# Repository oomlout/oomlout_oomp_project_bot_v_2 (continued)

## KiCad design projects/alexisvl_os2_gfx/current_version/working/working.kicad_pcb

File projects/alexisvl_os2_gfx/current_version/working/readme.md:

# os2
 
## summary 
* id: alexisvl_os2_gfx
* user: alexisvl
* name: os2
* board: gfx
* repo: https://github.com/alexisvl/os2
* src_file_repo_kicad_pcb: sch/gfx/gfx.kicad_pcb
* src_file_repo_kicad_pcb_link: https://github.com/alexisvl/os2/tree/trunk/sch/gfx/gfx.kicad_pcb
* src_file_repo_kicad_sch: sch/gfx/gfx.kicad_sch
* src_file_repo_kicad_sch_link: https://github.com/alexisvl/os2/tree/trunk/sch/gfx/gfx.kicad_sch

* src_file_repo_sch: sch/gfx/gfx.sch
* src_file_repo_sch_link: https://github.com/alexisvl/os2/tree/trunk/sch/gfx/gfx.sch
* full details link: https://github.com/oomlout/oomlout_oomp_project_bot_v_2/tree/main/projects/alexisvl_os2_gfx/current_version/working  

## schematic  
  
[schematic (pdf)](working_schematic.pdf) 

[schematic 1 (pdf)](working_1_schematic.pdf) 

## pcb  

[board (pdf)](working.pdf)  

## working_bom
| Id | Designator | Footprint | Quantity | Designation | Supplier and ref |  | None | 
| --- | --- | --- | --- | --- | --- | --- | --- | 
| 1 | R9,R33,R7,R8,R31 | R_Axial_DIN0207_L6.3mm_D2.5mm_P10.16mm_Horizontal | 5 | 499k |  |  | [''] | 
| 2 | R38,R23,R22,R37 | R_Axial_DIN0207_L6.3mm_D2.5mm_P10.16mm_Horizontal | 4 | 1k6 |  |  | [''] | 
| 3 | R18,R21 | R_Axial_DIN0207_L6.3mm_D2.5mm_P10.16mm_Horizontal | 2 | 4k99 |  |  | [''] | 
| 4 | C5,C1,C2,C3 | C_Disc_D4.7mm_W2.5mm_P5.00mm | 4 | 100p |  |  | [''] | 
| 5 | R34,R10,R36,R35,R32 | R_Axial_DIN0207_L6.3mm_D2.5mm_P10.16mm_Horizontal | 5 | 249k |  |  | [''] | 
| 6 | RV1,RV2 | stock_pot | 2 | 5k |  |  | [''] | 
| 7 | CD1 | CP_Radial_D8.0mm_P3.50mm | 1 | 470Âµ |  |  | [''] | 
| 8 | U18 | DIP-28_W15.24mm_Socket_LongPads | 1 | W27C512 |  |  | [''] | 
| 9 | P1 | DIN41612_B_3x32_Horizontal | 1 | DIN41612_M_3x32 |  |  | [''] | 
| 10 | CD40,CD43 | CP_Radial_D5.0mm_P2.00mm | 2 | 47Âµ |  |  | [''] | 
| 11 | D1,D3,D2 | D_DO-35_SOD27_P10.16mm_Horizontal | 3 | 1N4148 |  |  | [''] | 
| 12 | R2 | R_Axial_DIN0207_L6.3mm_D2.5mm_P10.16mm_Horizontal | 1 | 22k |  |  | [''] | 
| 13 | U8,U3,U7 | DIP-16_W7.62mm | 3 | 'HC109 |  |  | [''] | 
| 14 | Q4,Q6,Q1,Q7,Q5 | TO-92 | 5 | 2N3904 |  |  | [''] | 
| 15 | U11,U12,U13,U4 | DIP-16_W7.62mm | 4 | 'HC161 |  |  | [''] | 
| 16 | R30,R25 | R_Axial_DIN0207_L6.3mm_D2.5mm_P10.16mm_Horizontal | 2 | 6k2 |  |  | [''] | 
| 17 | R13,R12,R11,R14,R15 | R_Axial_DIN0207_L6.3mm_D2.5mm_P10.16mm_Horizontal | 5 | 68k |  |  | [''] | 
| 18 | RV6,RV3 | stock_pot | 2 | 50 |  |  | [''] | 
| 19 | Q3,Q2 | TO-92 | 2 | 2N7000 |  |  | [''] | 
| 20 | RV4 | stock_pot | 1 | 20k |  |  | [''] | 
| 21 | U10,U5,U9,U19 | DIP-14_W7.62mm | 4 | 'HC02 |  |  | [''] | 
| 22 | U15 | DIP-20_W7.62mm | 1 | 'AHC245 |  |  | [''] | 
| 23 | R41,R45,R26,R46 | R_Axial_DIN0207_L6.3mm_D2.5mm_P10.16mm_Horizontal | 4 | 75 |  |  | [''] | 
| 24 | U2 | DIP-14_W7.62mm | 1 | 'HC14 |  |  | [''] | 
| 25 | R3 | R_Axial_DIN0207_L6.3mm_D2.5mm_P10.16mm_Horizontal | 1 | 10k |  |  | [''] | 
| 26 | U21,U20 | DIP-8_W7.62mm | 2 | NE5532 |  |  | [''] | 
| 27 | RV5,RV7 | stock_pot | 2 | 10k |  |  | [''] | 
| 28 | R27,R42 | R_Axial_DIN0207_L6.3mm_D2.5mm_P10.16mm_Horizontal | 2 | 100 |  |  | [''] | 
| 29 | R40 | R_Axial_DIN0207_L6.3mm_D2.5mm_P10.16mm_Horizontal | 1 | 820 |  |  | [''] | 
| 30 | U14,U16 | DIP-20_W7.62mm | 2 | 'AHCT273 |  |  | [''] | 
| 31 | R20 | R_Axial_DIN0207_L6.3mm_D2.5mm_P10.16mm_Horizontal | 1 | 8k2 |  |  | [''] | 
| 32 | R4 | R_Axial_DIN0207_L6.3mm_D2.5mm_P10.16mm_Horizontal | 1 | 10 |  |  | [''] | 
| 33 | R24,R17 | R_Axial_DIN0207_L6.3mm_D2.5mm_P10.16mm_Horizontal | 2 | 7k5 |  |  | [''] | 
| 34 | R6 | R_Axial_DIN0207_L6.3mm_D2.5mm_P10.16mm_Horizontal | 1 | 3k3 |  |  | [''] | 
| 35 | R39 | R_Axial_DIN0207_L6.3mm_D2.5mm_P10.16mm_Horizontal | 1 | 3k |  |  | [''] | 
| 36 | R28,R43,R29,R44 | R_Axial_DIN0309_L9.0mm_D3.2mm_P12.70mm_Horizontal | 4 | 1k |  |  | [''] | 
| 37 | U1 | Oscillator_DIP-8 | 1 | 1MHz |  |  | [''] | 
| 38 | R1 | R_Axial_DIN0207_L6.3mm_D2.5mm_P10.16mm_Horizontal | 1 | 82k |  |  | [''] | 
| 39 | U17 | DIP-16_W7.62mm | 1 | 'HC237 |  |  | [''] | 
| 40 | U6 | DIP-14_W7.62mm | 1 | 'HC10 |  |  | [''] | 
| 41 | RN1 | R_Array_SIP10 | 1 | 1k |  |  | [''] | 
| 42 | R16 | R_Axial_DIN0207_L6.3mm_D2.5mm_P10.16mm_Horizontal | 1 | 15k |  |  | [''] | 
| 43 | R5 | R_Axial_DIN0207_L6.3mm_D2.5mm_P10.16mm_Horizontal | 1 | 6k8 |  |  | [''] | 
| 44 | R19 | R_Axial_DIN0207_L6.3mm_D2.5mm_P10.16mm_Horizontal | 1 | 18k |  |  | [''] | 
| 45 | CD18,CD45,CD17,CD15,CD11,CD21,CD2,CD12,CD4,CD41,CD20,CD3,CD10,CD14,CD7,CD8,CD13,CD6,CD9,CD44,CD16,CD5,CD19,CD42 | C_0805_2012Metric_Pad1.15x1.40mm_HandSolder | 24 | 1Âµ |  |  | [''] | 

## bom_schematic
no data

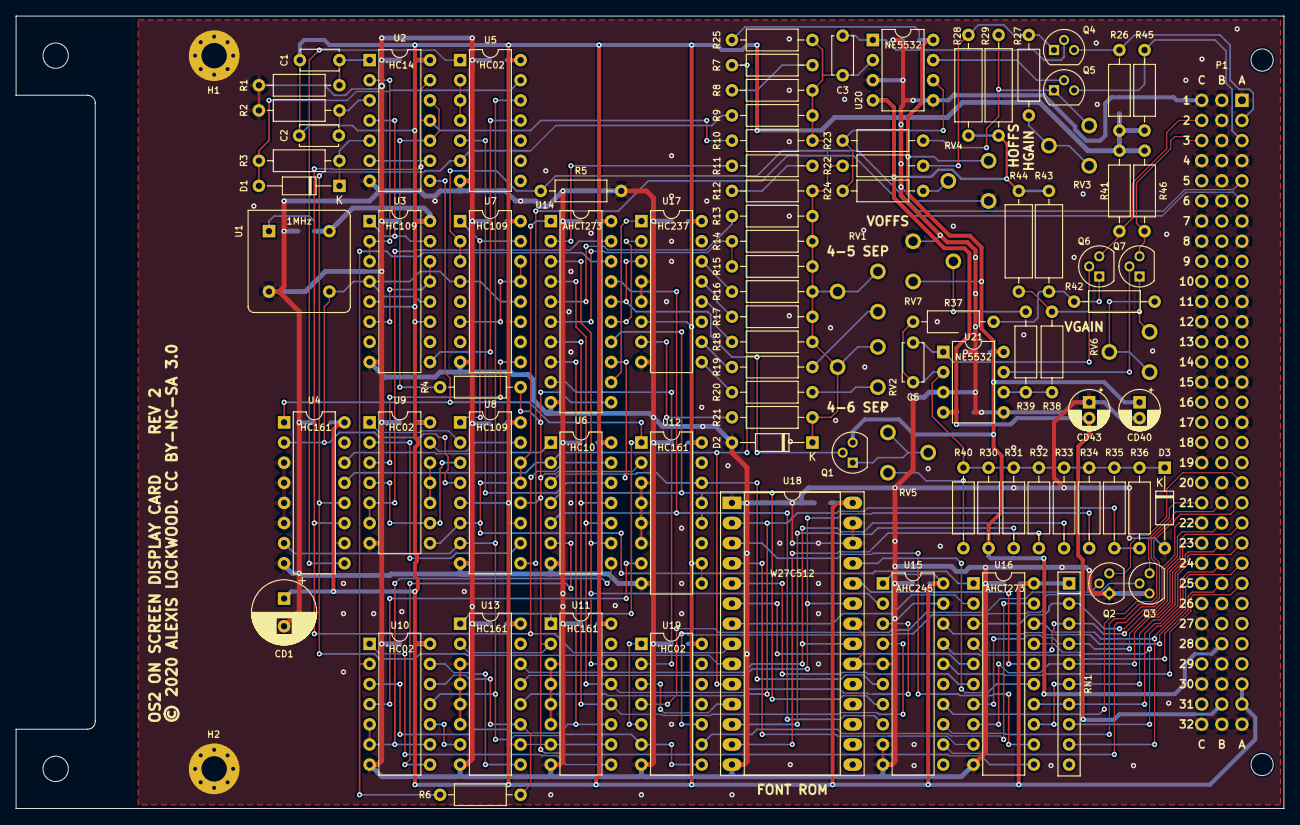
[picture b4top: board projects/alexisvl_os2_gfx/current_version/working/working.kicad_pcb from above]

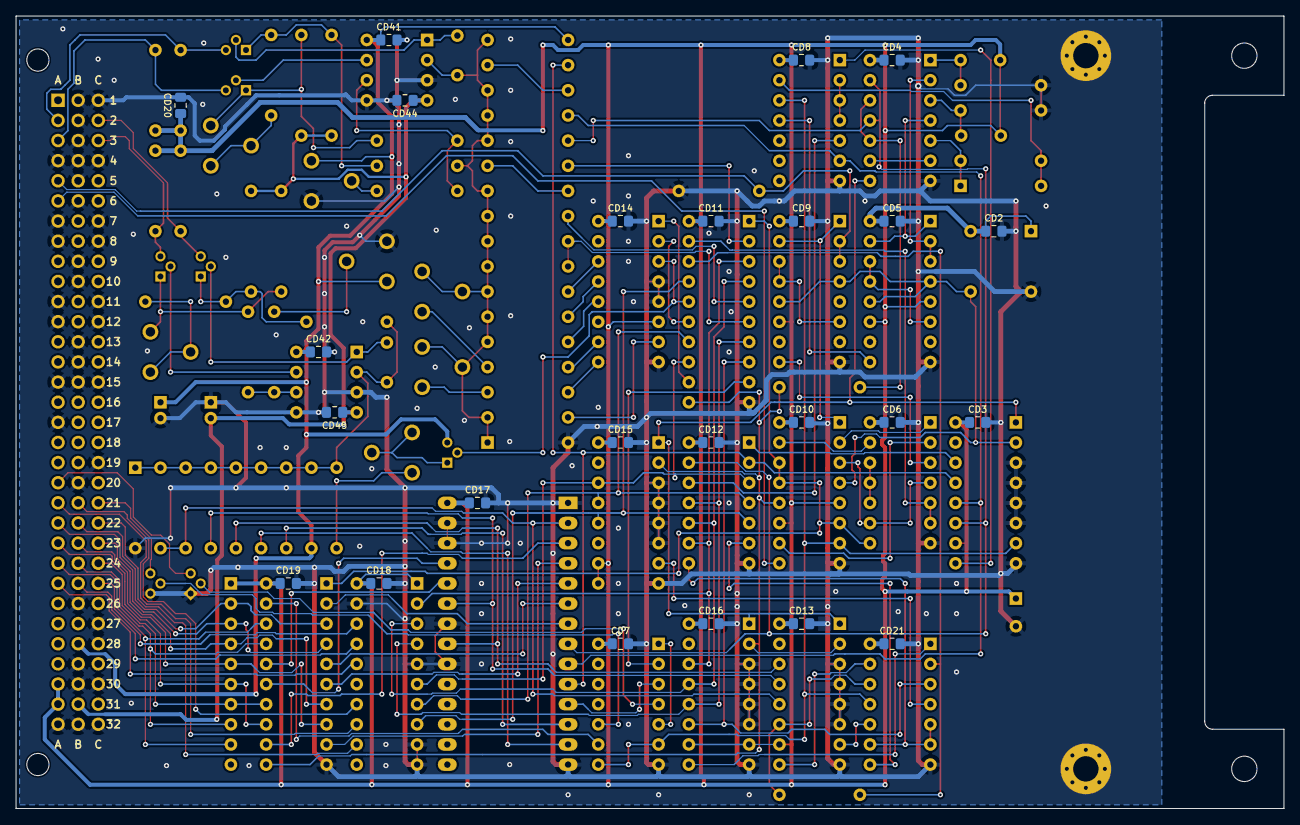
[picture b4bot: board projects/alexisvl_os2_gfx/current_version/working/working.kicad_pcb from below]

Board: 2 copper layers, 160.0 x 100.0 mm, 119 parts (24 on the bottom side), 124 nets.

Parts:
C1, C2, C3, C5: 100p; C_Disc_D4.7mm_W2.5mm_P5.00mm
CD1: 470µ; CP_Radial_D8.0mm_P3.50mm
CD2, CD3, CD4, CD5, CD6, CD7, CD8, CD9, CD10, CD11, CD12, CD13, CD14, CD15, CD16, CD17, CD18, CD19, CD20, CD21, CD41, CD42, CD44, CD45: 1µ; C_0805_2012Metric_Pad1.15x1.40mm_HandSolder
CD40, CD43: 47µ; CP_Radial_D5.0mm_P2.00mm
D1, D2, D3: 1N4148; D_DO-35_SOD27_P10.16mm_Horizontal
H1, H2: HOLE; MountingHole_3.2mm_M3_Pad_Via
P1: DIN41612_M_3x32; DIN41612_B_3x32_Horizontal
Q1, Q4, Q5, Q6, Q7: 2N3904; TO-92
Q2, Q3: 2N7000; TO-92
R1: 82k; R_Axial_DIN0207_L6.3mm_D2.5mm_P10.16mm_Horizontal
R2: 22k; R_Axial_DIN0207_L6.3mm_D2.5mm_P10.16mm_Horizontal
R3: 10k; R_Axial_DIN0207_L6.3mm_D2.5mm_P10.16mm_Horizontal
R4: 10; R_Axial_DIN0207_L6.3mm_D2.5mm_P10.16mm_Horizontal
R5: 6k8; R_Axial_DIN0207_L6.3mm_D2.5mm_P10.16mm_Horizontal
R6: 3k3; R_Axial_DIN0207_L6.3mm_D2.5mm_P10.16mm_Horizontal
R7, R8, R9, R31, R33: 499k; R_Axial_DIN0207_L6.3mm_D2.5mm_P10.16mm_Horizontal
R10, R32, R34, R35, R36: 249k; R_Axial_DIN0207_L6.3mm_D2.5mm_P10.16mm_Horizontal
R11, R12, R13, R14, R15: 68k; R_Axial_DIN0207_L6.3mm_D2.5mm_P10.16mm_Horizontal
R16: 15k; R_Axial_DIN0207_L6.3mm_D2.5mm_P10.16mm_Horizontal
R17, R24: 7k5; R_Axial_DIN0207_L6.3mm_D2.5mm_P10.16mm_Horizontal
R18, R21: 4k99; R_Axial_DIN0207_L6.3mm_D2.5mm_P10.16mm_Horizontal
R19: 18k; R_Axial_DIN0207_L6.3mm_D2.5mm_P10.16mm_Horizontal
R20: 8k2; R_Axial_DIN0207_L6.3mm_D2.5mm_P10.16mm_Horizontal
R22, R23, R37, R38: 1k6; R_Axial_DIN0207_L6.3mm_D2.5mm_P10.16mm_Horizontal
R25, R30: 6k2; R_Axial_DIN0207_L6.3mm_D2.5mm_P10.16mm_Horizontal
R26, R41, R45, R46: 75; R_Axial_DIN0207_L6.3mm_D2.5mm_P10.16mm_Horizontal
R27, R42: 100; R_Axial_DIN0207_L6.3mm_D2.5mm_P10.16mm_Horizontal
R28, R29, R43, R44: 1k; R_Axial_DIN0309_L9.0mm_D3.2mm_P12.70mm_Horizontal
R39: 3k; R_Axial_DIN0207_L6.3mm_D2.5mm_P10.16mm_Horizontal
R40: 820; R_Axial_DIN0207_L6.3mm_D2.5mm_P10.16mm_Horizontal
RN1: 1k; R_Array_SIP10
RV1, RV2: 5k; stock_pot
RV3, RV6: 50; stock_pot
RV4: 20k; stock_pot
RV5, RV7: 10k; stock_pot
U1: 1MHz; Oscillator_DIP-8
U2: 'HC14; DIP-14_W7.62mm
U3, U7, U8: 'HC109; DIP-16_W7.62mm
U4, U11, U12, U13: 'HC161; DIP-16_W7.62mm
U5, U9, U10, U19: 'HC02; DIP-14_W7.62mm
U6: 'HC10; DIP-14_W7.62mm
U14, U16: 'AHCT273; DIP-20_W7.62mm
U15: 'AHC245; DIP-20_W7.62mm
U17: 'HC237; DIP-16_W7.62mm
U18: W27C512; DIP-28_W15.24mm_Socket_LongPads
U20, U21: NE5532; DIP-8_W7.62mm

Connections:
+15V: CD40.1, CD41.1, CD42.1, P1.B28, Q1.3 (C), R25.2, R30.2, RV4.3, RV7.3, U20.8 (V+), U21.8 (V+)
-15V: CD43.2, CD44.1, CD45.1, P1.B31, R28.1, R29.1, R43.1, R44.1, U20.4 (V-), U21.4 (V-)
/CHAR0: U16.2 (Q0), U18.7 (A3)
/CHAR1: U16.5 (Q1), U18.6 (A4)
/CHAR2: U16.6 (Q2), U18.5 (A5)
/CHAR3: U16.9 (Q3), U18.4 (A6)
/CHAR4: U16.12 (Q4), U18.3 (A7)
/CHAR5: U16.15 (Q5), U18.25 (A8)
/CHAR6: U16.16 (Q6), U18.24 (A9)
/DESCENDER0: R31.2, U18.12 (D1)
/DESCENDER1: R32.2, U18.13 (D2)
/DONE#: U8.10 (Q), U9.2
/DONEREQ: U9.5, U9.6, U14.19 (Q7)
/FLD0: U14.12 (Q4), U17.1 (A0)
/FLD1: U14.15 (Q5), U17.2 (A1)
/FLD2: Q1.2 (B), U14.16 (Q6), U17.3 (A2)
/FLDREQ0: U6.3, U12.14 (Q0), U14.13 (D4), U15.6 (A4)
/FLDREQ1: U6.4, U12.13 (Q1), U14.14 (D5), U15.7 (A5)
/FLDREQ2: U6.5, U12.12 (Q2), U14.17 (D6), U15.8 (A6)
/HDOT0: R7.2, U4.13 (Q1), U6.2, U18.10 (A0)
/HDOT1: R9.2, U4.12 (Q2), U5.6, U18.9 (A1)
/HDOT2: R10.2, U2.11, U2.13, U4.11 (Q3), U6.13, U18.8 (A2)
/INTEN#: U16.19 (Q7), U19.9
/INTERFIELD_BLANK: U14.9 (Q3), U19.2
/LASTDOT: U4.9 (~Pe), U5.1
/LASTFLD#: U6.6, U10.8
/LASTPOS#: U6.8, U10.5, U10.6, U10.9
/LINE0: R33.2, U13.14 (Q0), U18.21 (A10)
/LINE1: R34.2, U13.13 (Q1), U18.23 (A11)
/LINE2: R35.2, R36.2, U13.12 (Q2), U18.2 (A12)
/PIX_BLANK: U18.11 (D0), U19.3
/POS0: R11.2, U14.2 (Q0)
/POS1: R13.2, U14.5 (Q1)
/POS2: R14.2, R15.2, U14.6 (Q2)
/POSREQ0: U6.9, U11.14 (Q0), U14.3 (D0), U15.2 (A0)
/POSREQ1: U6.10, U11.13 (Q1), U14.4 (D1), U15.3 (A1)
/POSREQ2: U6.11, U11.12 (Q2), U14.7 (D2), U15.4 (A2)
/PREBLANK: U10.3, U11.11 (Q3), U14.8 (D3)
/PREDONE: R6.2, U10.12, U13.11 (Q3)
/PREDONE': R6.1, U10.2, U14.18 (D7)
/~POR: U7.1 (R), U7.15 (R), U8.1 (R)
A2: P1.A2, Q4.3 (C), R26.1
A3: P1.A3, Q5.3 (C), R45.2
A5: P1.A5, R5.2, U7.2 (J), U7.3 (K)
A6: P1.A6, U8.9 (Q)
A20: P1.A20, Q2.3 (D)
A21: P1.A21, U15.13 (B5)
A22: P1.A22, RN1.3 (R2), U16.4 (D1)
A23: P1.A23, RN1.6 (R5), U16.13 (D4)
A24: P1.A24, RN1.9 (R8), U16.18 (D7)
A25: P1.A25, U15.16 (B2)
B21: P1.B21, U15.14 (B4)
B22: P1.B22, RN1.2 (R1), U16.3 (D0)
B23: P1.B23, RN1.5 (R4), U16.8 (D3)
B24: P1.B24, RN1.8 (R7), U16.17 (D6)
B25: P1.B25, U15.17 (B1)
C2: P1.C2, Q6.3 (C), R41.1
C3: P1.C3, Q7.3 (C), R46.2
C21: P1.C21, Q3.3 (D)
C22: P1.C22, U15.12 (B6)
C23: P1.C23, RN1.4 (R3), U16.7 (D2)
C24: P1.C24, RN1.7 (R6), U16.14 (D5)
C25: P1.C25, U15.18 (B0)
CLK: U1.5 (OUT), U3.4 (C), U3.12 (C), U4.2 (CK), U7.4 (C), U7.12 (C), U8.4 (C)
GND: CD1.2, CD2.2, CD3.2, CD4.2, CD5.2, CD6.2, CD7.2, CD8.2, CD9.2, CD10.2, CD11.2, CD12.2, CD13.2, CD14.2, CD15.2, CD16.2, CD17.2, CD18.2, CD19.2, CD20.2, CD21.2, CD40.2, CD41.2, CD42.2, CD43.1, CD44.2, CD45.2, D2.2 (A), D3.2 (A), H1.1, H2.1, P1.A1, P1.A4, P1.A7, P1.A8, P1.A11, P1.A12, P1.A15, P1.A17, P1.A32, P1.B1, P1.B2, P1.B3, P1.B4, P1.B5, P1.B6, P1.B9, P1.B10, P1.B13, P1.B14, P1.B15, P1.B20, P1.B26, P1.B29, P1.B30, P1.B32, P1.C1, P1.C4, P1.C7, P1.C8, P1.C11, P1.C12, P1.C15, P1.C19, P1.C27, P1.C28, P1.C30, P1.C32, Q2.1 (S), Q3.1 (S), R1.2, R2.2, R5.1, RV4.1, RV7.1, U1.4 (GND), U2.7 (GND), U3.8 (GND), U4.3 (P0), U4.4 (P1), U4.5 (P2), U4.6 (P3), U4.8 (GND), U5.7 (GND), U6.7 (GND), U7.8 (GND), U8.8 (GND), U9.7 (GND), U10.7 (GND), U11.3 (P0), U11.4 (P1), U11.5 (P2), U11.6 (P3), U11.8 (GND), U12.3 (P0), U12.4 (P1), U12.5 (P2), U12.6 (P3), U12.8 (GND), U13.3 (P0), U13.4 (P1), U13.5 (P2), U13.6 (P3), U13.8 (GND), U14.10 (GND), U15.5 (A3), U15.9 (A7), U15.10 (GND), U15.19 (CE), U16.10 (GND), U17.4 (~LE), U17.5 (~E1), U17.8 (GND), U18.1 (A15), U18.14 (GND), U18.20 (~CE), U18.22 (~OE), U18.26 (A13), U18.27 (A14), U19.7 (GND), U20.3 (+), U20.5 (+), U21.3 (+), U21.5 (+)
unnamed: C1.2, R1.1, U2.1
unnamed: C2.2, R2.1, U2.3
unnamed: C3.1, D2.1 (K), R8.1, R9.1, R10.1, R12.1, R13.1, R14.1, R15.1, R16.1, R17.1, R18.1, R21.1, R22.1, R25.1, RV1.2, RV1.3, RV2.2, RV2.3, U20.2 (-)
unnamed: C3.2, Q4.2 (B), U20.1
unnamed: C5.1, D3.1 (K), R30.1, R31.1, R32.1, R33.1, R34.1, R35.1, R36.1, R37.1, R40.1, U21.2 (-)
unnamed: C5.2, Q6.2 (B), U21.1
unnamed: D1.1 (K), R3.2, U2.5
unnamed: D1.2 (A), R3.1, U5.13
unnamed: Q1.1 (E), RV5.1, RV5.2
unnamed: Q2.2 (G), U19.4
unnamed: Q3.2 (G), U19.10
unnamed: Q4.1 (E), R22.2, R27.1, R28.2
unnamed: Q5.1 (E), R23.1, R29.2, RV3.3
unnamed: Q5.2 (B), U20.7
unnamed: Q6.1 (E), R37.2, R42.1, R43.2
unnamed: Q7.1 (E), R38.1, R44.2, RV6.3
unnamed: Q7.2 (B), U21.7
unnamed: R4.1, U2.10, U2.12
unnamed: R7.1, R8.2
unnamed: R11.1, R12.2
unnamed: R16.2, U17.14 (Y1)
unnamed: R17.2, U17.13 (Y2)
unnamed: R18.2, U17.12 (Y3)
unnamed: R19.1, RV1.1
unnamed: R19.2, U17.10 (Y5)
unnamed: R20.1, RV2.1
unnamed: R20.2, U17.9 (Y6)
unnamed: R21.2, U17.7 (Y7)
unnamed: R23.2, R24.1, U20.6 (-)
unnamed: R24.2, RV4.2
unnamed: R27.2, RV3.1, RV3.2
unnamed: R38.2, R39.1, U21.6 (-)
unnamed: R39.2, RV7.2
unnamed: R40.2, RV5.3
unnamed: R42.2, RV6.1, RV6.2
unnamed: U2.2, U3.2 (J), U3.3 (K)
unnamed: U2.4, U3.1 (R), U3.15 (R)
unnamed: U2.6, U2.9
unnamed: U3.6 (Q), U3.13 (K), U3.14 (J)
unnamed: U4.14 (Q0), U6.1
unnamed: U5.2, U5.3, U5.4
unnamed: U5.5, U6.12
unnamed: U7.9 (Q), U9.3
unnamed: U7.6 (Q), U7.13 (K), U7.14 (J)
unnamed: U8.2 (J), U9.1
unnamed: U8.3 (K), U9.4, U9.9
unnamed: U8.15 (R), U9.13
unnamed: U9.10, U9.11, U9.12
unnamed: U10.1, U11.9 (~Pe)
unnamed: U10.4, U12.7 (ENP)
unnamed: U10.10, U13.7 (ENP)
unnamed: U10.13, U13.9 (~Pe)
unnamed: U19.1, U19.5
POR: U3.9 (Q), U5.11
POSCLK: R4.2, U8.12 (C), U11.2 (CK), U12.2 (CK), U13.2 (CK), U14.11 (Cp), U16.11 (Cp)
RST#: U2.8, U4.1 (~MR), U11.1 (~MR), U12.1 (~MR), U13.1 (~MR)
RUN: U8.6 (Q), U8.13 (K), U8.14 (J), U9.8, U14.1 (~Mr), U16.1 (~Mr)
RUN#: U4.7 (ENP), U5.12, U8.7 (Q), U10.11, U19.6, U19.8
VCC: C1.1, C2.1, CD1.1, CD2.1, CD3.1, CD4.1, CD5.1, CD6.1, CD7.1, CD8.1, CD9.1, CD10.1, CD11.1, CD12.1, CD13.1, CD14.1, CD15.1, CD16.1, CD17.1, CD18.1, CD19.1, CD20.1, CD21.1, P1.A30, P1.A31, R26.2, R41.2, R45.1, R46.1, RN1.1 (common), U1.1 (EN), U1.8 (Vcc), U2.14 (VCC), U3.5 (S), U3.11 (S), U3.16 (VCC), U4.10 (ENT), U4.16 (VCC), U5.14 (VCC), U6.14 (VCC), U7.11 (S), U7.16 (VCC), U8.5 (S), U8.11 (S), U8.16 (VCC), U9.14 (VCC), U10.14 (VCC), U11.7 (ENP), U11.10 (ENT), U11.16 (VCC), U12.9 (~Pe), U12.10 (ENT), U12.16 (VCC), U13.10 (ENT), U13.16 (VCC), U14.20 (VCC), U15.1 (A->B), U15.20 (VCC), U16.20 (VCC), U17.6 (E2), U17.16 (VCC), U18.28 (VCC), U19.14 (VCC)

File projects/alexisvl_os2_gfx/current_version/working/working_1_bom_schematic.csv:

"Source:","C:\gh\oomlout_oomp_project_bot_v_2\projects\alexisvl_os2_gfx\current_version\working\working_1.kicad_sch"
"Date:","24/09/2023 22:51:26"
"Tool:","Eeschema 7.0.6"
"Generator:","C:/Program Files/KiCad/7.0/bin/scripting/plugins/bom_csv_grouped_by_value_with_fp.py"
"Component Count:","119"
"Ref","Qnty","Value","Cmp name","Footprint","Description","Vendor","DNP"
"C1, C2, C3, C5","4","100p","C","Capacitor_THT:C_Disc_D4.7mm_W2.5mm_P5.00mm","","",""
"CD1","1","470µ","CP","Capacitor_THT:CP_Radial_D8.0mm_P3.50mm","","",""
"CD2, CD3, CD4, CD5, CD6, CD7, CD8, CD9, CD10, CD11, CD12, CD13, CD14, CD15, CD16, CD17, CD18, CD19, CD20, CD21, CD41, CD42, CD44, CD45","24","1µ","C","Capacitor_SMD:C_0805_2012Metric_Pad1.15x1.40mm_HandSolder","","",""
"CD40, CD43","2","47µ","CP","Capacitor_THT:CP_Radial_D5.0mm_P2.00mm","","",""
"D1, D2, D3","3","1N4148","D","Diode_THT:D_DO-35_SOD27_P10.16mm_Horizontal","","",""
"H1, H2","2","HOLE","Conn_01x01_Male","MountingHole:MountingHole_3.2mm_M3_Pad_Via","Generic connector, single row, 01x01, script generated (kicad-library-utils/schlib/autogen/connector/)","",""
"P1","1","DIN41612_M_3x32","DIN41612_M_3x32","alt-libs:DIN41612_B_3x32_Horizontal","","",""
"Q1, Q4, Q5, Q6, Q7","5","2N3904","Q_NPN_EBC","Package_TO_SOT_THT:TO-92","","",""
"Q2, Q3","2","2N7000","Q_NMOS_SGD","Package_TO_SOT_THT:TO-92","","",""
"R1","1","82k","R","Resistor_THT:R_Axial_DIN0207_L6.3mm_D2.5mm_P10.16mm_Horizontal","","",""
"R2","1","22k","R","Resistor_THT:R_Axial_DIN0207_L6.3mm_D2.5mm_P10.16mm_Horizontal","","",""
"R3","1","10k","R","Resistor_THT:R_Axial_DIN0207_L6.3mm_D2.5mm_P10.16mm_Horizontal","","",""
"R4","1","10","R","Resistor_THT:R_Axial_DIN0207_L6.3mm_D2.5mm_P10.16mm_Horizontal","","",""
"R5","1","6k8","R","Resistor_THT:R_Axial_DIN0207_L6.3mm_D2.5mm_P10.16mm_Horizontal","","",""
"R6","1","3k3","R","Resistor_THT:R_Axial_DIN0207_L6.3mm_D2.5mm_P10.16mm_Horizontal","","",""
"R7, R8, R9, R31, R33","5","499k","R","Resistor_THT:R_Axial_DIN0207_L6.3mm_D2.5mm_P10.16mm_Horizontal","","",""
"R10, R32, R34, R35, R36","5","249k","R","Resistor_THT:R_Axial_DIN0207_L6.3mm_D2.5mm_P10.16mm_Horizontal","","",""
"R11, R12, R13, R14, R15","5","68k","R","Resistor_THT:R_Axial_DIN0207_L6.3mm_D2.5mm_P10.16mm_Horizontal","","",""
"R16","1","15k","R","Resistor_THT:R_Axial_DIN0207_L6.3mm_D2.5mm_P10.16mm_Horizontal","","",""
"R17, R24","2","7k5","R","Resistor_THT:R_Axial_DIN0207_L6.3mm_D2.5mm_P10.16mm_Horizontal","","",""
"R18, R21","2","4k99","R","Resistor_THT:R_Axial_DIN0207_L6.3mm_D2.5mm_P10.16mm_Horizontal","","",""
"R19","1","18k","R","Resistor_THT:R_Axial_DIN0207_L6.3mm_D2.5mm_P10.16mm_Horizontal","","",""
"R20","1","8k2","R","Resistor_THT:R_Axial_DIN0207_L6.3mm_D2.5mm_P10.16mm_Horizontal","","",""
"R22, R23, R37, R38","4","1k6","R","Resistor_THT:R_Axial_DIN0207_L6.3mm_D2.5mm_P10.16mm_Horizontal","","",""
"R25, R30","2","6k2","R","Resistor_THT:R_Axial_DIN0207_L6.3mm_D2.5mm_P10.16mm_Horizontal","","",""
"R26, R41, R45, R46","4","75","R","Resistor_THT:R_Axial_DIN0207_L6.3mm_D2.5mm_P10.16mm_Horizontal","","",""
"R27, R42","2","100","R","Resistor_THT:R_Axial_DIN0207_L6.3mm_D2.5mm_P10.16mm_Horizontal","","",""
"R28, R29, R43, R44","4","1k","R_HW","Resistor_THT:R_Axial_DIN0309_L9.0mm_D3.2mm_P12.70mm_Horizontal","","",""
"R39","1","3k","R","Resistor_THT:R_Axial_DIN0207_L6.3mm_D2.5mm_P10.16mm_Horizontal","","",""
"R40","1","820","R","Resistor_THT:R_Axial_DIN0207_L6.3mm_D2.5mm_P10.16mm_Horizontal","","",""
"RN1","1","1k","R_Network09","Resistor_THT:R_Array_SIP10","9 resistor network, star topology, bussed resistors, small symbol","",""
"RV1, RV2","2","5k","AltDevice:R_POT_TRIM_7","alt-libs:stock_pot","","",""
"RV3, RV6","2","50","AltDevice:R_POT_TRIM_2","alt-libs:stock_pot","","",""
"RV4","1","20k","AltDevice:R_POT_TRIM_4","alt-libs:stock_pot","","",""
"RV5, RV7","2","10k","AltDevice:R_POT_TRIM_3","alt-libs:stock_pot","","",""
"U1","1","1MHz","CXO_DIP8","Oscillator:Oscillator_DIP-8","Crystal Clock Oscillator, DIP8-style metal package","",""
"U2","1","'HC14","74HC14","Package_DIP:DIP-14_W7.62mm","","",""
"U3, U7, U8","3","'HC109","AltDevice:74LS109_6","Package_DIP:DIP-16_W7.62mm","","",""
"U4, U11, U12, U13","4","'HC161","74LS161","Package_DIP:DIP-16_W7.62mm","","",""
"U5, U9, U10, U19","4","'HC02","74HC02","Package_DIP:DIP-14_W7.62mm","quad 2-input NOR gate","",""
"U6","1","'HC10","74LS10","Package_DIP:DIP-14_W7.62mm","Triple 3-input NAND","",""
"U14, U16","2","'AHCT273","74HC273","Package_DIP:DIP-20_W7.62mm","8-bit D Flip-Flop, reset","",""
"U15","1","'AHC245","74LS245","Package_DIP:DIP-20_W7.62mm","Octal BUS Transceivers, 3-State outputs","",""
"U17","1","'HC237","74HC237","Package_DIP:DIP-16_W7.62mm","3-to-8 line decoder/multiplexer with address latches, DIP-16/SOIC-16/SSOP-16","",""
"U18","1","W27C512","27C512","Package_DIP:DIP-28_W15.24mm_Socket_LongPads","OTP EPROM 512 KiBit","",""
"U20, U21","2","NE5532","NE5532","Package_DIP:DIP-8_W7.62mm","Dual Low-Noise Operational Amplifiers, DIP-8/SOIC-8","",""

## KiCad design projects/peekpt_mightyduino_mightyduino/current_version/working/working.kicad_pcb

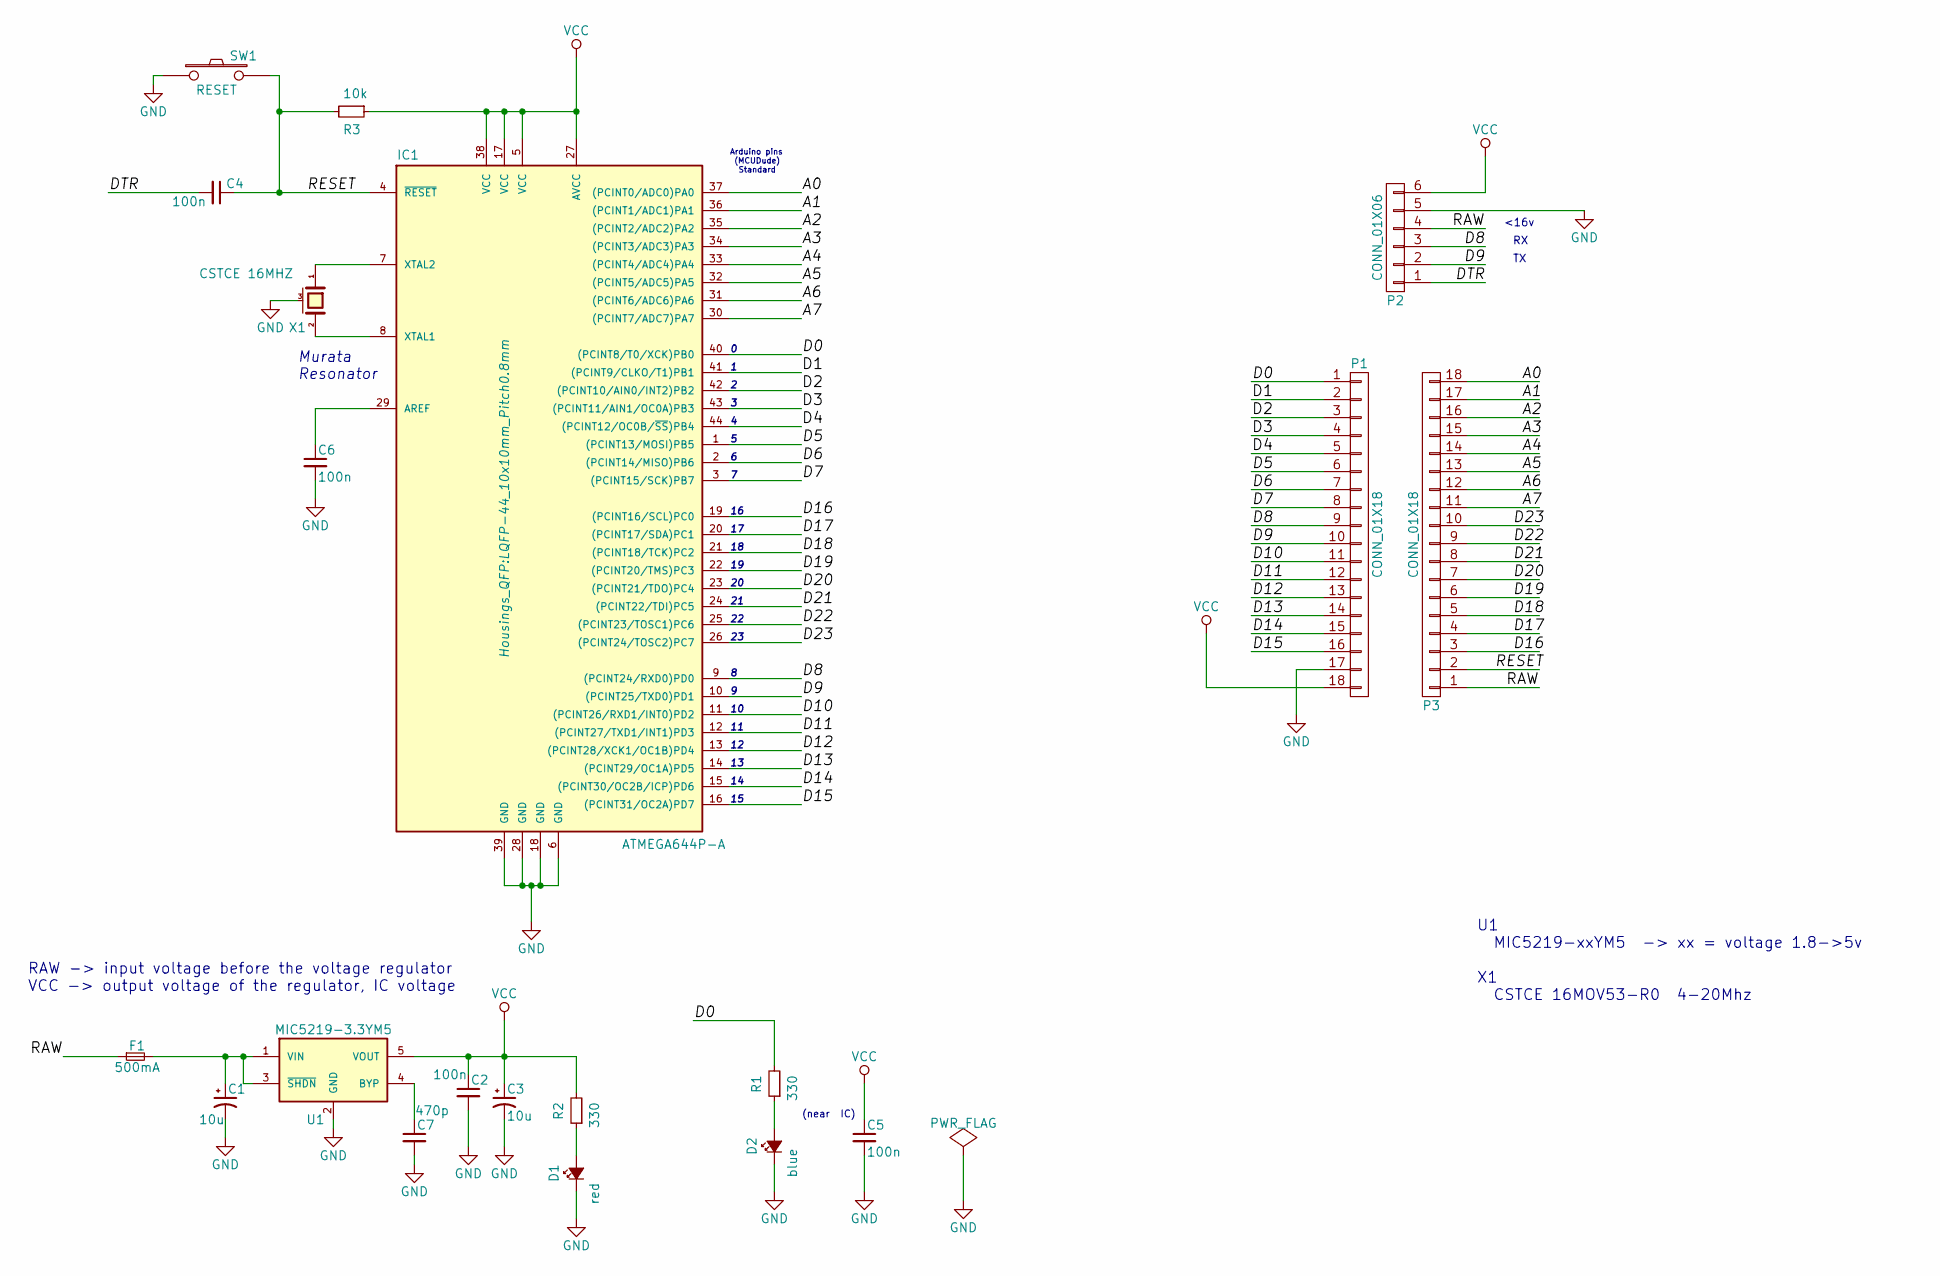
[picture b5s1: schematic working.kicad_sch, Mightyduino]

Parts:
C1, C3: 10u; TantalC_SizeA_EIA-3216_Reflow
C2, C4, C5, C6: 100n; C_0805
C7: 470p; C_0805
D1: red; LED_0805
D2: blue; LED_0805
F1: 500mA; C_0805_HandSoldering
IC1: ATMEGA644P-A; LQFP-44_10x10mm_Pitch0.8mm
P1, P3: CONN_01X18; Pin_Header_Straight_1x18
P2: CONN_01X06; Pin_Header_Straight_1x06
R1, R2: 330; R_0805
R3: 10k; R_0805
SW1: RESET; SW_SPST_TL3342
U1: MIC5219-3.3YM5; SOT-23-5
X1: CSTCE 16MHZ; CSTCEv2

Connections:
/A0: IC1.37 ((PCINT0/ADC0)PA0), P3.18
/A1: IC1.36 ((PCINT1/ADC1)PA1), P3.17
/A2: IC1.35 ((PCINT2/ADC2)PA2), P3.16
/A3: IC1.34 ((PCINT3/ADC3)PA3), P3.15
/A4: IC1.33 ((PCINT4/ADC4)PA4), P3.14
/A5: IC1.32 ((PCINT5/ADC5)PA5), P3.13
/A6: IC1.31 ((PCINT6/ADC6)PA6), P3.12
/A7: IC1.30 ((PCINT7/ADC7)PA7), P3.11
/D0: IC1.40 ((PCINT8/T0/XCK)PB0), P1.1, R1.2
/D1: IC1.41 ((PCINT9/CLKO/T1)PB1), P1.2
/D2: IC1.42 ((PCINT10/AIN0/INT2)PB2), P1.3
/D3: IC1.43 ((PCINT11/AIN1/OC0A)PB3), P1.4
/D4: IC1.44 ((PCINT12/OC0B/~SS)PB4), P1.5
/D5: IC1.1 ((PCINT13/MOSI)PB5), P1.6
/D6: IC1.2 ((PCINT14/MISO)PB6), P1.7
/D7: IC1.3 ((PCINT15/SCK)PB7), P1.8
/D8: IC1.9 ((PCINT24/RXD0)PD0), P1.9, P2.3
/D9: IC1.10 ((PCINT25/TXD0)PD1), P1.10, P2.2
/D10: IC1.11 ((PCINT26/RXD1/INT0)PD2), P1.11
/D11: IC1.12 ((PCINT27/TXD1/INT1)PD3), P1.12
/D12: IC1.13 ((PCINT28/XCK1/OC1B)PD4), P1.13
/D13: IC1.14 ((PCINT29/OC1A)PD5), P1.14
/D14: IC1.15 ((PCINT30/OC2B/ICP)PD6), P1.15
/D15: IC1.16 ((PCINT31/OC2A)PD7), P1.16
/D16: IC1.19 ((PCINT16/SCL)PC0), P3.3
/D17: IC1.20 ((PCINT17/SDA)PC1), P3.4
/D18: IC1.21 ((PCINT18/TCK)PC2), P3.5
/D19: IC1.22 ((PCINT20/TMS)PC3), P3.6
/D20: IC1.23 ((PCINT21/TDO)PC4), P3.7
/D21: IC1.24 ((PCINT22/TDI)PC5), P3.8
/D22: IC1.25 ((PCINT23/TOSC1)PC6), P3.9
/D23: IC1.26 ((PCINT24/TOSC2)PC7), P3.10
/DTR: C4.2, P2.1
/RAW: F1.1, P2.4, P3.1
/RESET: C4.1, IC1.4 (~RESET), P3.2, R3.2, SW1.2
GND: C1.2, C2.2, C3.2, C5.2, C6.2, C7.2, D1.1 (K), D2.1 (K), IC1.6 (GND), IC1.18 (GND), IC1.28 (GND), IC1.39 (GND), P1.17, P2.5, SW1.1, U1.2 (GND), X1.3 (case)
unnamed: C1.1, F1.2, U1.1 (VIN), U1.3 (~SHDN)
unnamed: C6.1, IC1.29 (AREF)
unnamed: C7.1, U1.4 (BYP)
unnamed: D1.2 (A), R2.1
unnamed: D2.2 (A), R1.1
unnamed: IC1.7 (XTAL2), X1.1
unnamed: IC1.8 (XTAL1), X1.2
VCC: C2.1, C3.1, C5.1, IC1.5 (VCC), IC1.17 (VCC), IC1.27 (AVCC), IC1.38 (VCC), P1.18, P2.6, R2.2, R3.1, U1.5 (VOUT)

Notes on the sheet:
Arduino pins (MCUDude) Standard
(near IC)
U1 MIC5219-xxYM5 -> xx = voltage 1.8->5v X1 CSTCE 16MOV53-R0 4-20Mhz
RAW -> input voltage before the voltage regulator VCC -> output voltage of the regulator, IC voltage
Murata Resonator
<16v

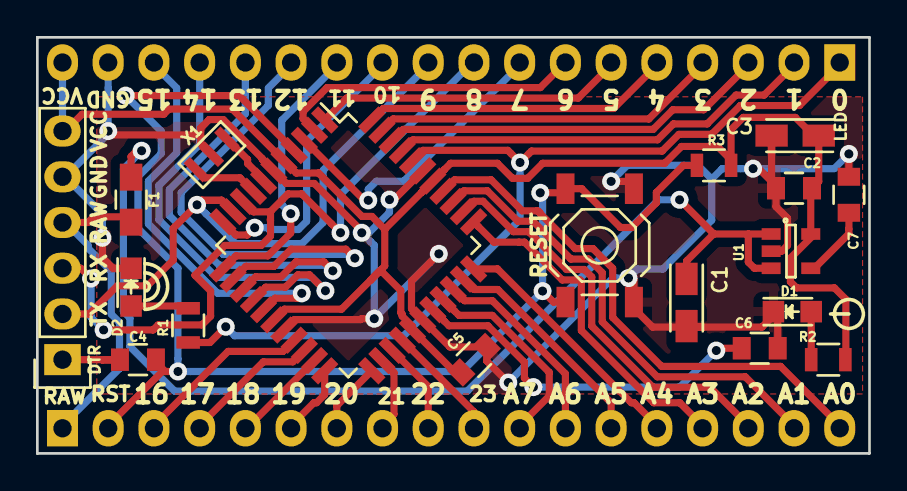
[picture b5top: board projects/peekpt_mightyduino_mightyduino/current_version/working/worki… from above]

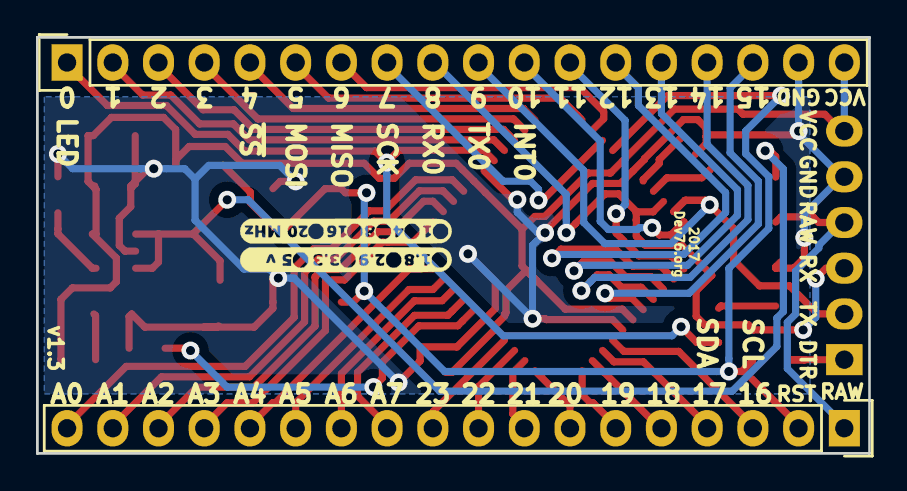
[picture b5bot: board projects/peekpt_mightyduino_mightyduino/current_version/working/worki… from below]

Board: 2 copper layers, 46.2 x 23.1 mm, 20 parts (2 on the bottom side), 44 nets.

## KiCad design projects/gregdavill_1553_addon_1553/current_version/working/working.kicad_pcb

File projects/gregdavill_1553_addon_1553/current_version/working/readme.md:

# 1553_addon
 
## summary 
* id: gregdavill_1553_addon_1553
* user: gregdavill
* name: 1553_addon
* board: 1553
* repo: https://github.com/gregdavill/1553-addon
* src_file_repo_kicad_pcb: 1553.kicad_pcb
* src_file_repo_kicad_pcb_link: https://github.com/gregdavill/1553-addon/tree/master/1553.kicad_pcb

* src_file_repo_sch: 1553.sch
* src_file_repo_sch_link: https://github.com/gregdavill/1553-addon/tree/master/1553.sch
* full details link: https://github.com/oomlout/oomlout_oomp_project_bot_v_2/tree/main/projects/gregdavill_1553_addon_1553/current_version/working

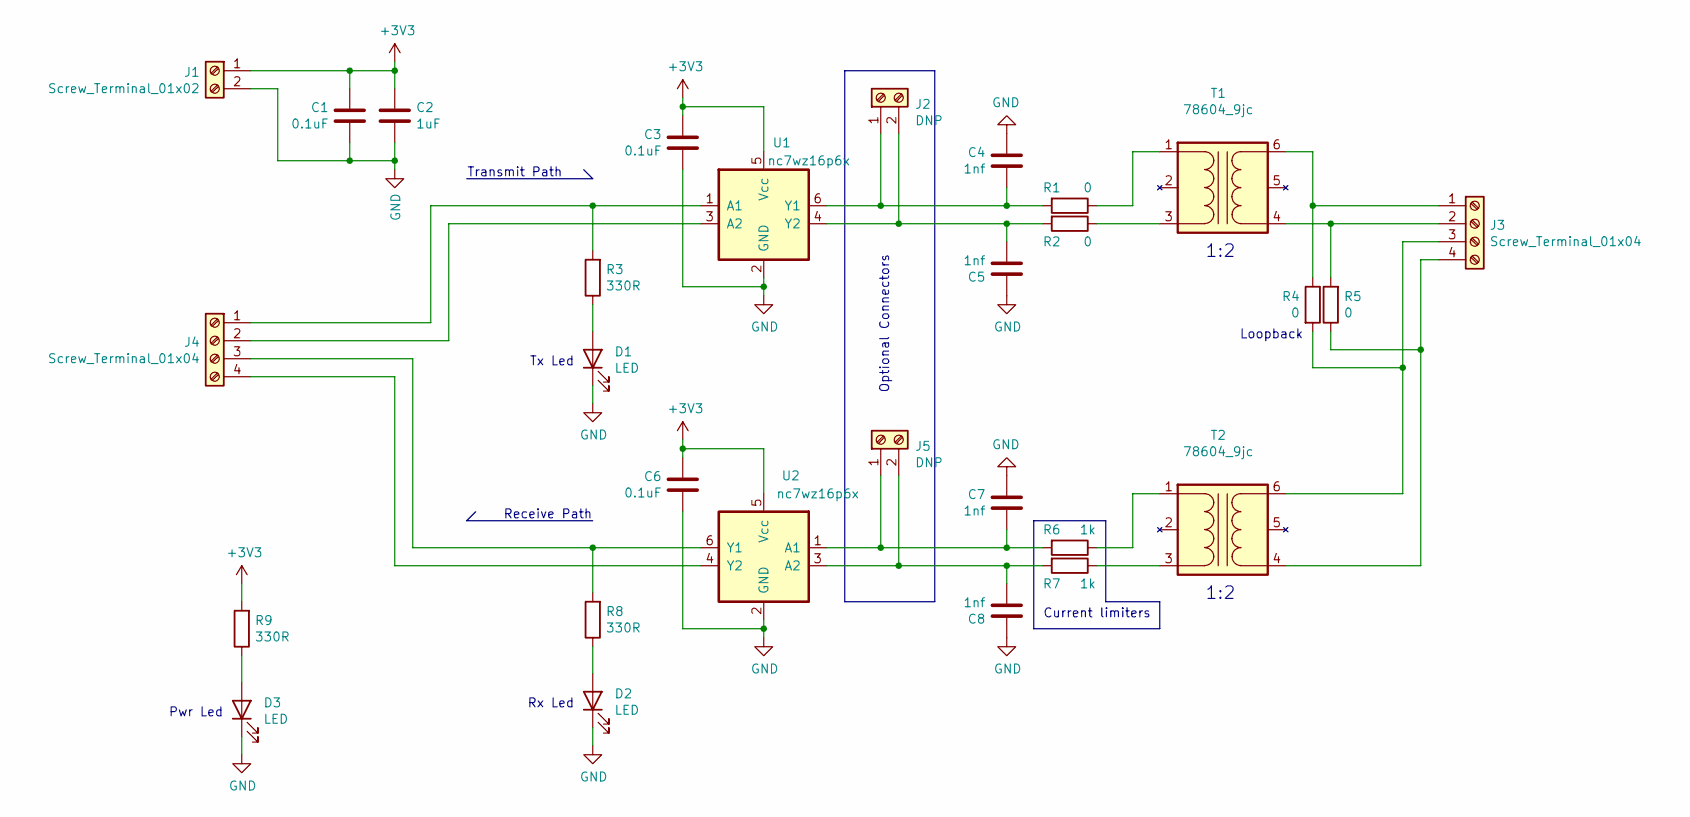
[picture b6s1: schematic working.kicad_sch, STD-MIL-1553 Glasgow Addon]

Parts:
C1, C3, C6: 0.1uF; C_0603_1608Metric
C2: 1uF; C_0603_1608Metric
C4, C5, C7, C8: 1nf; C_0603_1608Metric
D1, D2, D3: LED; LED_0603_1608Metric
J1: Screw_Terminal_01x02; TerminalBlock_TE_282834-2_1x02_P2.54mm_Horizontal
J2, J5: DNP; TerminalBlock_TE_282834-2_1x02_P2.54mm_Horizontal
J3, J4: Screw_Terminal_01x04; TerminalBlock_TE_282834-4_1x04_P2.54mm_Horizontal
R1, R2, R4, R5: 0; R_0603_1608Metric
R3, R8, R9: 330R; R_0603_1608Metric
R6, R7: 1k; R_0603_1608Metric
T1, T2: 78604_9jc; 786J
U1, U2: nc7wz16p6x; SOT-363_SC-70-6

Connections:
+3V3: C1.1, C2.1, C3.1, C6.1, J1.1, R9.2, U1.5 (Vcc), U2.5 (Vcc)
GND: C1.2, C2.2, C3.2, C4.1, C5.1, C6.2, C7.1, C8.1, D1.1 (K), D2.1 (K), D3.1 (K), J1.2, U1.2 (GND), U2.2 (GND)
unnamed: C4.2, J2.1, R1.2, U1.6 (Y1)
unnamed: C5.2, J2.2, R2.2, U1.4 (Y2)
unnamed: C7.2, J5.1, R6.2, U2.1 (A1)
unnamed: C8.2, J5.2, R7.2, U2.3 (A2)
unnamed: D1.2 (A), R3.1
unnamed: D2.2 (A), R8.1
unnamed: D3.2 (A), R9.1
unnamed: J3.1, R4.1, T1.6
unnamed: J3.2, R5.2, T1.4
unnamed: J3.3, R4.2, T2.6
unnamed: J3.4, R5.1, T2.4
unnamed: J4.1, R3.2, U1.1 (A1)
unnamed: J4.2, U1.3 (A2)
unnamed: J4.3, R8.2, U2.6 (Y1)
unnamed: J4.4, U2.4 (Y2)
unnamed: R1.1, T1.1
unnamed: R2.1, T1.3
unnamed: R6.1, T2.1
unnamed: R7.1, T2.3

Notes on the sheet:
Transmit Path
Receive Path
1:2
Current limiters
Rx Led
Loopback
Optional Connectors
Tx Led
Pwr Led

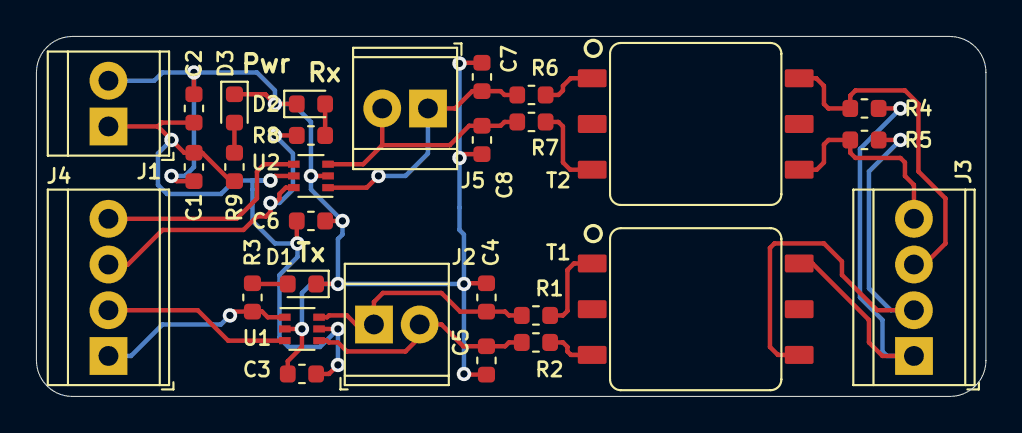
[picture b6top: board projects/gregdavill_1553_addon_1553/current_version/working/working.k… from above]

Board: 2 copper layers, 52.8 x 20.0 mm, 29 parts (0 on the bottom side), 21 nets.
